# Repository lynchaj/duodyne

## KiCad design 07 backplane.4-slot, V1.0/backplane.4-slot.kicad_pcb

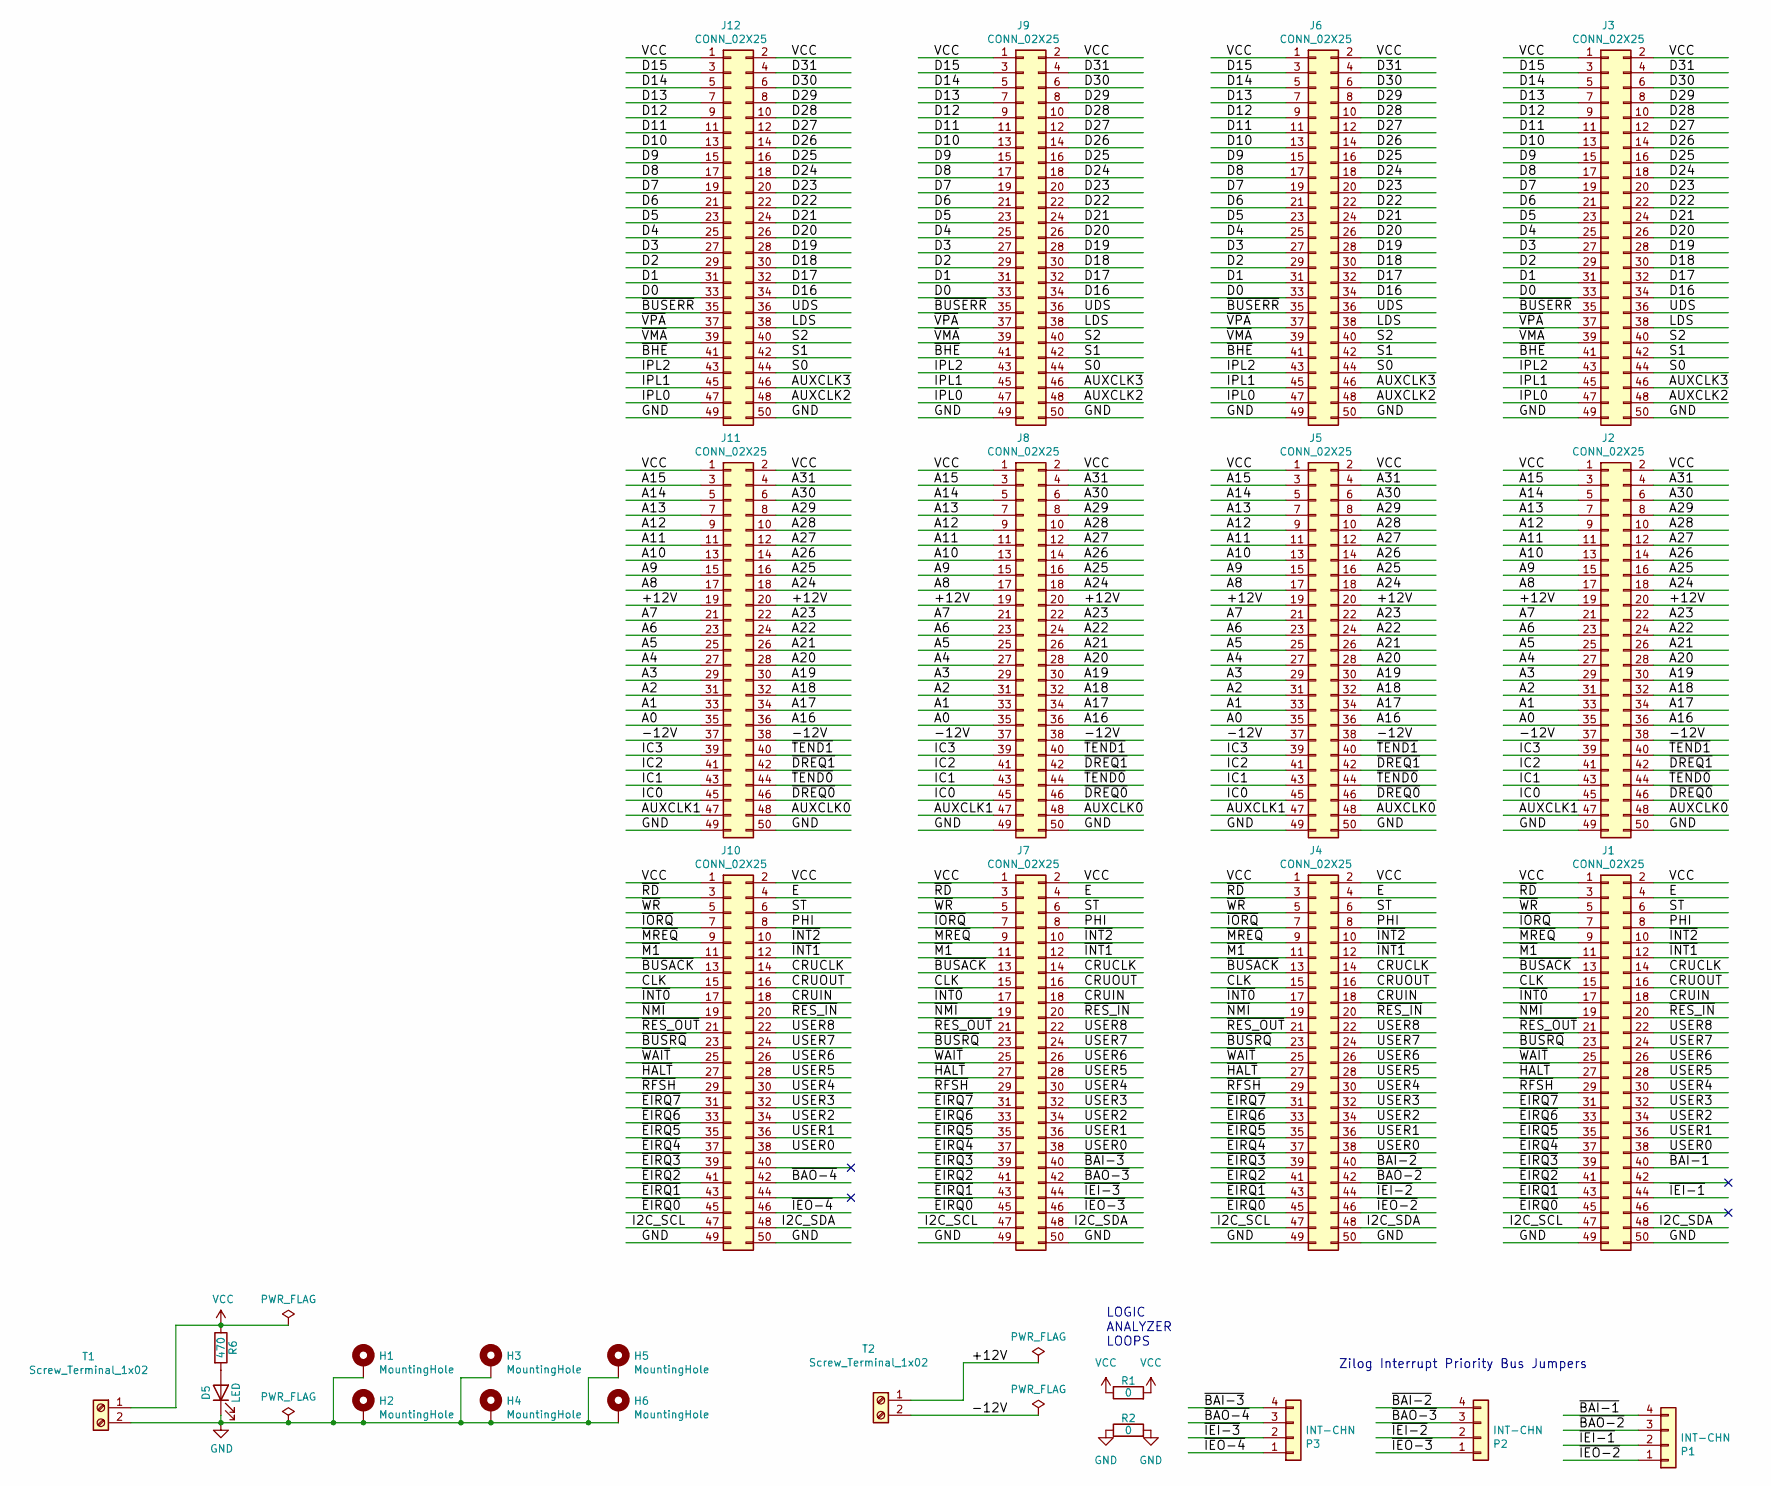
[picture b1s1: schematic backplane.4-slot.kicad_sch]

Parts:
D5: LED; LED_D3.0mm
H1, H2, H3, H4, H5, H6: MountingHole; MountingHole_3.2mm_M3_Pad
J1, J2, J3, J4, J5, J6, J7, J8, J9, J10, J11, J12: CONN_02X25; PinSocket_2x25_P2.54mm_Vertical
P1, P2, P3: INT-CHN; PinHeader_1x04_P2.54mm_Vertical
R1, R2: 0; R_Axial_DIN0207_L6.3mm_D2.5mm_P7.62mm_Horizontal
R6: 470; R_Axial_DIN0207_L6.3mm_D2.5mm_P7.62mm_Horizontal
T1, T2: Screw_Terminal_1x02; TerminalBlock_Phoenix_MKDS-1,5-2-5.08_1x02_P5.08mm_Horizont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

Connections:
/+12V: J2.19, J2.20, J5.19, J5.20, J8.19, J8.20, J11.19, J11.20, T2.1
/-12V: J2.37, J2.38, J5.37, J5.38, J8.37, J8.38, J11.37, J11.38, T2.2
/A0: J2.35, J5.35, J8.35, J11.35
/A1: J2.33, J5.33, J8.33, J11.33
/A2: J2.31, J5.31, J8.31, J11.31
/A3: J2.29, J5.29, J8.29, J11.29
/A4: J2.27, J5.27, J8.27, J11.27
/A5: J2.25, J5.25, J8.25, J11.25
/A6: J2.23, J5.23, J8.23, J11.23
/A7: J2.21, J5.21, J8.21, J11.21
/A8: J2.17, J5.17, J8.17, J11.17
/A9: J2.15, J5.15, J8.15, J11.15
/A10: J2.13, J5.13, J8.13, J11.13
/A11: J2.11, J5.11, J8.11, J11.11
/A12: J2.9, J5.9, J8.9, J11.9
/A13: J2.7, J5.7, J8.7, J11.7
/A14: J2.5, J5.5, J8.5, J11.5
/A15: J2.3, J5.3, J8.3, J11.3
/A16: J2.36, J5.36, J8.36, J11.36
/A17: J2.34, J5.34, J8.34, J11.34
/A18: J2.32, J5.32, J8.32, J11.32
/A19: J2.30, J5.30, J8.30, J11.30
/A20: J2.28, J5.28, J8.28, J11.28
/A21: J2.26, J5.26, J8.26, J11.26
/A22: J2.24, J5.24, J8.24, J11.24
/A23: J2.22, J5.22, J8.22, J11.22
/A24: J2.18, J5.18, J8.18, J11.18
/A25: J2.16, J5.16, J8.16, J11.16
/A26: J2.14, J5.14, J8.14, J11.14
/A27: J2.12, J5.12, J8.12, J11.12
/A28: J2.10, J5.10, J8.10, J11.10
/A29: J2.8, J5.8, J8.8, J11.8
/A30: J2.6, J5.6, J8.6, J11.6
/A31: J2.4, J5.4, J8.4, J11.4
/AUXCLK0: J2.48, J5.48, J8.48, J11.48
/AUXCLK1: J2.47, J5.47, J8.47, J11.47
/AUXCLK2: J3.48, J6.48, J9.48, J12.48
/AUXCLK3: J3.46, J6.46, J9.46, J12.46
/CLK: J1.15, J4.15, J7.15, J10.15
/CRUCLK: J1.14, J4.14, J7.14, J10.14
/CRUIN: J1.18, J4.18, J7.18, J10.18
/CRUOUT: J1.16, J4.16, J7.16, J10.16
/D0: J3.33, J6.33, J9.33, J12.33
/D1: J3.31, J6.31, J9.31, J12.31
/D2: J3.29, J6.29, J9.29, J12.29
/D3: J3.27, J6.27, J9.27, J12.27
/D4: J3.25, J6.25, J9.25, J12.25
/D5: J3.23, J6.23, J9.23, J12.23
/D6: J3.21, J6.21, J9.21, J12.21
/D7: J3.19, J6.19, J9.19, J12.19
/D8: J3.17, J6.17, J9.17, J12.17
/D9: J3.15, J6.15, J9.15, J12.15
/D10: J3.13, J6.13, J9.13, J12.13
/D11: J3.11, J6.11, J9.11, J12.11
/D12: J3.9, J6.9, J9.9, J12.9
/D13: J3.7, J6.7, J9.7, J12.7
/D14: J3.5, J6.5, J9.5, J12.5
/D15: J3.3, J6.3, J9.3, J12.3
/D16: J3.34, J6.34, J9.34, J12.34
/D17: J3.32, J6.32, J9.32, J12.32
/D18: J3.30, J6.30, J9.30, J12.30
/D19: J3.28, J6.28, J9.28, J12.28
/D20: J3.26, J6.26, J9.26, J12.26
/D21: J3.24, J6.24, J9.24, J12.24
/D22: J3.22, J6.22, J9.22, J12.22
/D23: J3.20, J6.20, J9.20, J12.20
/D24: J3.18, J6.18, J9.18, J12.18
/D25: J3.16, J6.16, J9.16, J12.16
/D26: J3.14, J6.14, J9.14, J12.14
/D27: J3.12, J6.12, J9.12, J12.12
/D28: J3.10, J6.10, J9.10, J12.10
/D29: J3.8, J6.8, J9.8, J12.8
/D30: J3.6, J6.6, J9.6, J12.6
/D31: J3.4, J6.4, J9.4, J12.4
/E: J1.4, J4.4, J7.4, J10.4
/I2C_SCL: J1.47, J4.47, J7.47, J10.47
/I2C_SDA: J1.48, J4.48, J7.48, J10.48
/IC0: J2.45, J5.45, J8.45, J11.45
/IC1: J2.43, J5.43, J8.43, J11.43
/IC2: J2.41, J5.41, J8.41, J11.41
/IC3: J2.39, J5.39, J8.39, J11.39
/IPL0: J3.47, J6.47, J9.47, J12.47
/IPL1: J3.45, J6.45, J9.45, J12.45
/IPL2: J3.43, J6.43, J9.43, J12.43
/LDS: J3.38, J6.38, J9.38, J12.38
/PHI: J1.8, J4.8, J7.8, J10.8
/S0: J3.44, J6.44, J9.44, J12.44
/S1: J3.42, J6.42, J9.42, J12.42
/S2: J3.40, J6.40, J9.40, J12.40
/ST: J1.6, J4.6, J7.6, J10.6
/UDS: J3.36, J6.36, J9.36, J12.36
/USER0: J1.38, J4.38, J7.38, J10.38
/USER1: J1.36, J4.36, J7.36, J10.36
/USER2: J1.34, J4.34, J7.34, J10.34
/USER3: J1.32, J4.32, J7.32, J10.32
/USER4: J1.30, J4.30, J7.30, J10.30
/USER5: J1.28, J4.28, J7.28, J10.28
/USER6: J1.26, J4.26, J7.26, J10.26
/USER7: J1.24, J4.24, J7.24, J10.24
/USER8: J1.22, J4.22, J7.22, J10.22
/~BAI-1: J1.40, P1.4
/~BAI-2: J4.40, P2.4
/~BAI-3: J7.40, P3.4
/~BAO-2: J4.42, P1.3
/~BAO-3: J7.42, P2.3
/~BAO-4: J10.42, P3.3
/~BHE: J3.41, J6.41, J9.41, J12.41
/~BUSACK: J1.13, J4.13, J7.13, J10.13
/~BUSERR: J3.35, J6.35, J9.35, J12.35
/~BUSRQ: J1.23, J4.23, J7.23, J10.23
/~DREQ0: J2.46, J5.46, J8.46, J11.46
/~DREQ1: J2.42, J5.42, J8.42, J11.42
/~EIRQ0: J1.45, J4.45, J7.45, J10.45
/~EIRQ1: J1.43, J4.43, J7.43, J10.43
/~EIRQ2: J1.41, J4.41, J7.41, J10.41
/~EIRQ3: J1.39, J4.39, J7.39, J10.39
/~EIRQ4: J1.37, J4.37, J7.37, J10.37
/~EIRQ5: J1.35, J4.35, J7.35, J10.35
/~EIRQ6: J1.33, J4.33, J7.33, J10.33
/~EIRQ7: J1.31, J4.31, J7.31, J10.31
/~HALT: J1.27, J4.27, J7.27, J10.27
/~IEI-1: J1.44, P1.2
/~IEI-2: J4.44, P2.2
/~IEI-3: J7.44, P3.2
/~IEO-2: J4.46, P1.1
/~IEO-3: J7.46, P2.1
/~IEO-4: J10.46, P3.1
/~INT0: J1.17, J4.17, J7.17, J10.17
/~INT1: J1.12, J4.12, J7.12, J10.12
/~INT2: J1.10, J4.10, J7.10, J10.10
/~IORQ: J1.7, J4.7, J7.7, J10.7
/~M1: J1.11, J4.11, J7.11, J10.11
/~MREQ: J1.9, J4.9, J7.9, J10.9
/~NMI: J1.19, J4.19, J7.19, J10.19
/~RD: J1.3, J4.3, J7.3, J10.3
/~RES_IN: J1.20, J4.20, J7.20, J10.20
/~RES_OUT: J1.21, J4.21, J7.21, J10.21
/~RFSH: J1.29, J4.29, J7.29, J10.29
/~TEND0: J2.44, J5.44, J8.44, J11.44
/~TEND1: J2.40, J5.40, J8.40, J11.40
/~VMA: J3.39, J6.39, J9.39, J12.39
/~VPA: J3.37, J6.37, J9.37, J12.37
/~WAIT: J1.25, J4.25, J7.25, J10.25
/~WR: J1.5, J4.5, J7.5, J10.5
GND: D5.1 (K), H1.1, H2.1, H3.1, H4.1, H5.1, H6.1, J1.49, J1.50, J2.49, J2.50, J3.49, J3.50, J4.49, J4.50, J5.49, J5.50, J6.49, J6.50, J7.49, J7.50, J8.49, J8.50, J9.49, J9.50, J10.49, J10.50, J11.49, J11.50, J12.49, J12.50, R2.1, R2.2, T1.2
unnamed: D5.2 (A), R6.2
VCC: J1.1, J1.2, J2.1, J2.2, J3.1, J3.2, J4.1, J4.2, J5.1, J5.2, J6.1, J6.2, J7.1, J7.2, J8.1, J8.2, J9.1, J9.2, J10.1, J10.2, J11.1, J11.2, J12.1, J12.2, R1.1, R1.2, R6.1, T1.1

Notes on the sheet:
LOGIC ANALYZER LOOPS
Zilog Interrupt Priority Bus Jumpers

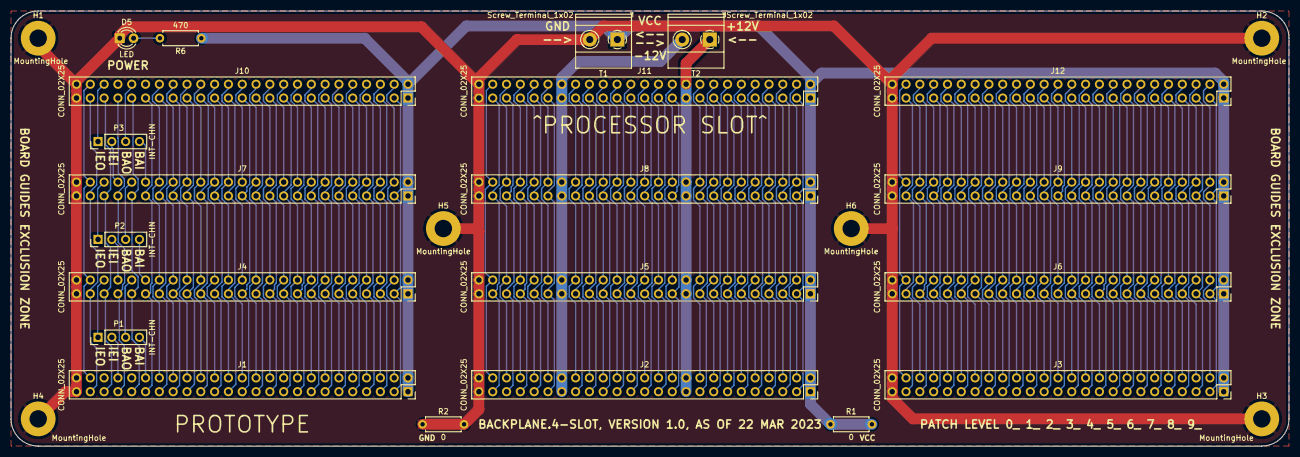
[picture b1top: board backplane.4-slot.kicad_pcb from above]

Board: 2 copper layers, 235.0 x 80.0 mm, 27 parts (0 on the bottom side), 147 nets.

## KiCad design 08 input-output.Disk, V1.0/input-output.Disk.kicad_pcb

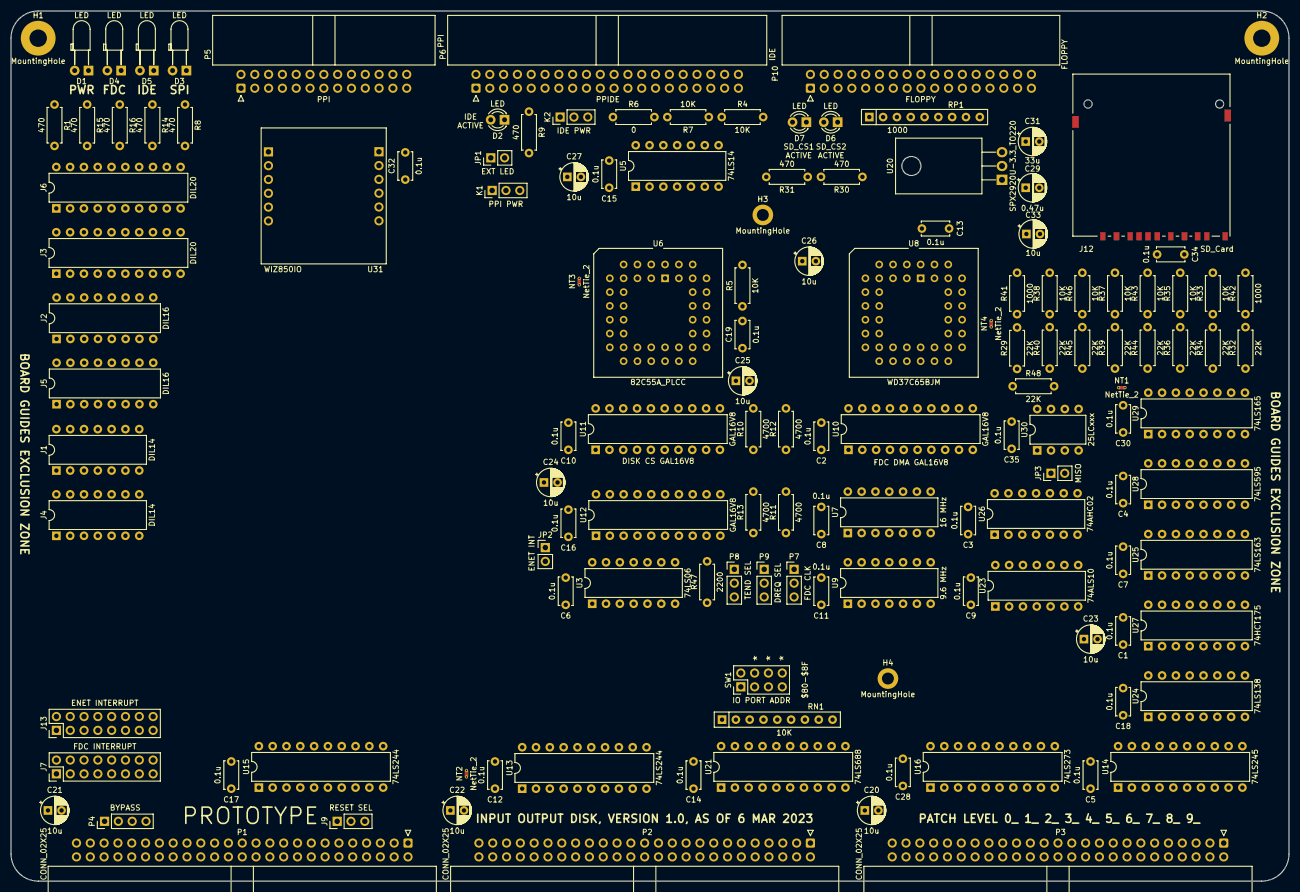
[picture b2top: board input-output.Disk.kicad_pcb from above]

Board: 2 copper layers, 235.0 x 160.0 mm, 136 parts (0 on the bottom side), 202 nets, no tracks yet.

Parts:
C1, C2, C3, C4, C5, C6, C7, C8, C9, C10, C11, C12, C13, C14, C15, C16, C17, C18, C19, C28, C30, C32, C34, C35: 0.1u; C_Disc_D5.0mm_W2.5mm_P5.00mm
C20, C21, C22, C23, C24, C25, C26, C27, C33: 10u; CP_Radial_D5.0mm_P2.50mm
C29: 0.47u; CP_Radial_D5.0mm_P2.50mm
C31: 33u; CP_Radial_D5.0mm_P2.50mm
D1, D3, D4, D5: LED; LED_D3.0mm_Horizontal_O3.81mm_Z2.0mm
D2, D6, D7: LED; LED_D3.0mm
H1, H2: MountingHole; MountingHole_3.2mm_M3_Pad
H3, H4: MountingHole; MountingHole_2.2mm_M2_DIN965_Pad
J1, J4: DIL14; DIP-14_W7.62mm
J2, J5: DIL16; DIP-16_W7.62mm
J3, J6: DIL20; DIP-20_W7.62mm
J7: FDC INTERRUPT; PinHeader_2x08_P2.54mm_Vertical
J9: RESET SEL; PinHeader_1x03_P2.54mm_Vertical
J12: SD_Card; SD_Card_Receptacle
J13: ENET INTERRUPT; PinHeader_2x08_P2.54mm_Vertical
JP1: EXT LED; PinHeader_1x02_P2.54mm_Vertical
JP2: ENET INT; PinHeader_1x02_P2.54mm_Vertical
JP3: MISO; PinHeader_1x02_P2.54mm_Vertical
K1: PPI PWR; PinHeader_1x03_P2.54mm_Vertical
K2: IDE PWR; PinHeader_1x03_P2.54mm_Vertical
NT1, NT2, NT3, NT4: NetTie_2; NetTie-2_THT_Pad0.3mm
P1, P2, P3: CONN_02X25; IDC-Header_2x25_P2.54mm_Horizontal
P4: BYPASS; PinHeader_1x04_P2.54mm_Vertical
P5: PPI; IDC-Header_2x13_P2.54mm_Horizontal
P6: IDE; IDC-Header_2x20_P2.54mm_Horizontal
P7: FDC CLK; PinHeader_1x03_P2.54mm_Vertical
P8: TEND SEL; PinHeader_1x03_P2.54mm_Vertical
P9: DREQ SEL; PinHeader_1x03_P2.54mm_Vertical
P10: FLOPPY; IDC-Header_2x17_P2.54mm_Horizontal
R1, R8, R9, R14, R15, R16, R30, R31: 470; R_Axial_DIN0207_L6.3mm_D2.5mm_P7.62mm_Horizontal
R4, R5, R7, R33, R35, R37, R38, R43, R46: 10K; R_Axial_DIN0207_L6.3mm_D2.5mm_P7.62mm_Horizontal
R6: 0; R_Axial_DIN0207_L6.3mm_D2.5mm_P7.62mm_Horizontal
R10, R11, R12, R13: 4700; R_Axial_DIN0207_L6.3mm_D2.5mm_P7.62mm_Horizontal
R29, R32, R34, R36, R39, R40, R44, R45, R48: 22K; R_Axial_DIN0207_L6.3mm_D2.5mm_P7.62mm_Horizontal
R41, R42: 1000; R_Axial_DIN0207_L6.3mm_D2.5mm_P7.62mm_Horizontal
R47: 2200; R_Axial_DIN0207_L6.3mm_D2.5mm_P7.62mm_Horizontal
RN1: 10K; R_Array_SIP9
RP1: 1000; R_Array_SIP9
SW1: IO PORT ADDR; PinHeader_2x04_P2.54mm_Vertical
U3: 74LS06; DIP-14_W7.62mm
U5: 74LS14; DIP-14_W7.62mm
U6: 82C55A_PLCC; PLCC-44_THT-Socket
U7: 16 MHz; DIP-14_W7.62mm
U8: WD37C65BJM; PLCC-44_THT-Socket
U9: 9.6 MHz; DIP-14_W7.62mm
U10, U11, U12: GAL16V8; DIP-20_W7.62mm
U13, U15: 74LS244; DIP-20_W7.62mm
U14: 74LS245; DIP-20_W7.62mm
U16: 74LS273; DIP-20_W7.62mm
U20: SPX2920U-3.3_TO220; TO-220-3_Horizontal_TabDown
U21: 74LS688; DIP-20_W7.62mm
U23: 74ALS10; DIP-14_W7.62mm
U24: 74LS138; DIP-16_W7.62mm
U25: 74LS163; DIP-16_W7.62mm
U26: 74AHC02; DIP-14_W7.62mm
U27: 74HCT175; DIP-16_W7.62mm
U28: 74LS595; DIP-16_W7.62mm
U29: 74LS165; DIP-16_W7.62mm
U30: 25LCxxx; DIP-8_W7.62mm
U31: WIZ850IO

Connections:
16MHZ-CLK: U7.8, U7.11, U8.26 (XT1)
+12V: P2.19, P2.20
-12V: P2.37, P2.38
/FDC/FDC_DMA: R12.2, U3.1, U8.15 (DMA)
/FDC/GND_PLCC: NT4.2, U8.34 (GND)
/FDC/PCVAL: RP1.8 (R7), U8.27 (PCVAL)
/FDC/RDY: P9.2, R11.1, U3.2
/FDC/~DCHG: P10.34, RP1.4 (R3), U8.40 (/DCHG)
/FDC/~DIRC: P10.18, U8.31 (/DIRC)
/FDC/~DS1: P10.14, U8.33 (/DS1)
/FDC/~DS2: P10.12, U8.35 (/DS2)
/FDC/~HS: P10.32, U8.28 (/HS)
/FDC/~IDX: P10.8, RP1.7 (R6), U8.43 (/IDX)
/FDC/~INT_FDC: J7.1, J7.3, J7.5, J7.7, J7.9, J7.11, J7.13, J7.15, U3.12
/FDC/~MO1: P10.10, U8.36 (/MO1/DS3)
/FDC/~MO2: P10.16, U8.37 (/MO2/DS4)
/FDC/~RDD: P10.30, RP1.3 (R2), U8.21 (/RDD)
/FDC/~RWC: P10.2, U8.39 (/RWC/RPM)
/FDC/~STEP: P10.20, U8.32 (/STEP)
/FDC/~TR00: P10.26, RP1.6 (R5), U8.42 (/TR00)
/FDC/~WD: P10.22, U8.30 (/WD)
/FDC/~WE: P10.24, U8.29 (/WE)
/FDC/~WP: P10.28, RP1.5 (R4), U8.41 (/WP)
/GAL/~CS_FDC_LED: D4.1 (K), U10.12 (IO8)
/PPIDE/CSEL: P6.28, R6.2
/PPIDE/DMARQ: P6.21, R7.2
/PPIDE/GND_PLCC: NT3.2, U6.8 (GND)
/PPIDE/PA0: P5.2, P6.17, U6.5 (PA0)
/PPIDE/PA1: P5.4, P6.15, U6.4 (PA1)
/PPIDE/PA2: P5.6, P6.13, U6.3 (PA2)
/PPIDE/PA3: P5.8, P6.11, U6.2 (PA3)
/PPIDE/PA4: P5.10, P6.9, U6.44 (PA4)
/PPIDE/PA5: P5.12, P6.7, U6.43 (PA5)
/PPIDE/PA6: P5.14, P6.5, U6.42 (PA6)
/PPIDE/PA7: P5.16, P6.3, R5.2, U6.41 (PA7)
/PPIDE/PB0: P5.18, P6.4, U6.20 (PB0)
/PPIDE/PB1: P5.20, P6.6, U6.21 (PB1)
/PPIDE/PB2: P5.22, P6.8, U6.22 (PB2)
/PPIDE/PB3: P5.24, P6.10, U6.24 (PB3)
/PPIDE/PB4: P5.23, P6.12, U6.25 (PB4)
/PPIDE/PB5: P5.21, P6.14, U6.26 (PB5)
/PPIDE/PB6: P5.19, P6.16, U6.27 (PB6)
/PPIDE/PB7: P5.17, P6.18, U6.28 (PB7)
/PPIDE/PC0: P5.1, P6.35, U6.16 (PC0)
/PPIDE/PC1: P5.3, P6.33, U6.17 (PC1)
/PPIDE/PC2: P5.5, P6.36, U6.18 (PC2)
/PPIDE/PC3: P5.7, U5.1, U6.19 (PC3)
/PPIDE/PC4: P5.9, U5.5, U6.15 (PC4)
/PPIDE/PC5: P5.11, U5.3, U6.14 (PC5)
/PPIDE/PC6: P5.13, U5.13, U6.13 (PC6)
/PPIDE/PC7: P5.15, U5.9, U6.11 (PC7)
/PPIDE/VCC_IDE: K2.2, P6.20
/PPIDE/VCC_PP: K1.2, P5.25
/PPIDE/~ACTIVE: D2.1 (K), JP1.2 (B), P6.39
/PPIDE/~DMACK: P6.29, R4.2
/PPIDE/~PC3: P6.37, U5.2
/PPIDE/~PC4: P6.38, U5.6
/PPIDE/~PC5: P6.23, U5.4
/PPIDE/~PC6: P6.25, U5.12
/PPIDE/~PC7: P6.1, U5.8
/WIZNET/D0: U28.15 (QA), U29.11 (D0)
/WIZNET/D1: U28.1 (QB), U29.12 (D1)
/WIZNET/D2: U28.2 (QC), U29.13 (D2)
/WIZNET/D3: U28.3 (QD), U29.14 (D3)
/WIZNET/D4: U28.4 (QE), U29.3 (D4)
/WIZNET/D5: U28.5 (QF), U29.4 (D5)
/WIZNET/D6: U28.6 (QG), U29.5 (D6)
/WIZNET/D7: U28.7 (QH), U29.6 (D7)
/WIZNET/MISO: J12.7 (DAT0), JP3.2 (B), R32.2, U28.14 (SER), U31.J2-6 (MISO)
/WIZNET/MOSI: J12.2 (CMD), R43.2, R44.2, U30.5 (MOSI), U31.J1-3 (MOSI)
/WIZNET/QD: U25.5 (D2), U25.6 (D3), U25.11 (Q3), U26.3, U26.6, U29.15 (~CE)
/WIZNET/RCO: U23.4, U25.15 (TC)
/WIZNET/SCK: J12.5 (CLK), R35.2, R36.2, U28.11 (SRCLK), U30.6 (SCK), U31.J1-4 (SCLK)
/WIZNET/~CLR: U23.6, U23.9, U25.1 (~MR)
/WIZNET/~CS0: R38.2, R40.2, U31.J1-5 (~SCN)
/WIZNET/~CS1: R33.2, R34.1, U30.1 (~CS)
/WIZNET/~CS2: J12.1 (CD/DAT3), R37.2, R39.2
/WIZNET/~CTRL_WR: U24.11 (O4), U27.9 (Cp)
/WIZNET/~ENET_INT: JP2.1 (A), U3.9
/WIZNET/~LATCH_WR: U16.11 (Cp), U24.10 (O5)
/WIZNET/~MOSI: U26.11, U29.7 (~Q7)
/WIZNET/~QD: U25.7 (CEP), U25.9 (~PE), U26.4
/WIZNET/~RST: R45.2, R46.2, U31.J2-5 (~RST)
/WIZNET/~SD_RDNTR: U23.1, U24.13 (O2)
/WIZNET/~SD_RDTR: U23.2, U23.3, U23.11, U23.13, U24.12 (O3)
/WIZNET/~SD_WRTR: U23.5, U23.10, U24.15 (O0), U29.1 (~PL)
/WIZNET/~SER_RD: U26.10, U28.13 (~OE)
/WIZNET/~TR: U23.8, U25.3 (D0), U25.4 (D1)
A0: P2.35, U13.2 (I0a)
A1: P2.33, U13.4 (I1a)
A2: P2.31, U13.6 (I2a)
A3: P2.29, U13.8 (I3a)
A4: P2.27, U13.11 (I0b)
A5: P2.25, U13.13 (I1b)
A6: P2.23, U13.15 (I2b)
A7: P2.21, U13.17 (I3b)
CLK: P1.15, U15.8 (I3a)
D0: P3.33, U14.2 (A0)
D1: P3.31, U14.3 (A1)
D2: P3.29, U14.4 (A2)
D3: P3.27, U14.5 (A3)
D4: P3.25, U14.6 (A4)
D5: P3.23, U14.7 (A5)
D6: P3.21, U14.8 (A6)
D7: P3.19, U14.9 (A7)
FDC-RESET: U8.20 (RST), U10.19 (IO1)
FDC-TC: U8.6 (TC), U10.18 (IO2)
GND: C1.2, C2.2, C3.2, C4.2, C5.2, C6.2, C7.2, C8.2, C9.2, C10.2, C11.2, C12.2, C13.2, C14.2, C15.2, C16.2, C17.2, C18.2, C19.2, C20.2, C21.2, C22.2, C23.2, C24.2, C25.2, C26.2, C27.2, C28.2, C29.2, C30.2, C31.2, C32.2, C33.2, C34.2, C35.2, D1.1 (K), D6.1 (K), D7.1 (K), H1.1, H2.1, J12.3 (VSS), J12.6 (VSS), J12.12 (SHELL1), J12.13 (SHELL2), K1.1, K2.1, NT2.1, NT3.1, NT4.1, P1.49, P1.50, P2.49, P2.50, P3.49, P3.50, P5.26, P6.2, P6.19, P6.22, P6.24, P6.26, P6.30, P6.40, P7.3, P10.1, P10.3, P10.5, P10.7, P10.9, P10.11, P10.13, P10.15, P10.17, P10.19, P10.21, P10.23, P10.25, P10.27, P10.29, P10.31, P10.33, R5.1, R6.1, R7.1, R10.1, R12.1, R34.2, R36.1, R39.1, R40.1, R44.1, R45.1, U3.7 (GND), U5.7 (GND), U7.4, U7.7, U9.4, U9.7, U10.10 (GND), U11.10 (GND), U12.10 (GND), U13.10 (GND), U14.10 (GND), U15.10 (GND), U16.10 (GND), U20.2 (GND), U21.10 (GND), U23.7 (GND), U24.8 (GND), U25.8 (GND), U26.7 (GND), U27.8 (GND), U28.8 (GND), U29.8 (GND), U30.4 (GND), U31.J1-1 (GND), U31.J1-2 (GND), U31.J2-1 (GND)
INT_FDC: R10.2, U3.13, U8.16 (IRQ)
unnamed: D1.2 (A), R1.1
unnamed: D2.2 (A), R8.1
unnamed: D3.1 (K), U11.16 (IO4)
unnamed: D3.2 (A), R14.1
unnamed: D4.2 (A), R15.1
unnamed: D5.1 (K), U11.15 (IO5)
unnamed: D5.2 (A), R16.1
unnamed: D6.2 (A), R30.2
unnamed: D7.2 (A), R31.2
unnamed: J9.2, U15.2 (I0a)
unnamed: J12.8 (DAT1), R42.2
unnamed: J12.9 (DAT2), R41.1
unnamed: J13.1, J13.3, J13.5, J13.7, J13.9, J13.11, J13.13, J13.15, U3.10
unnamed: JP1.1 (A), R9.1
unnamed: JP2.2 (B), U31.J1-6 (~INT)
unnamed: JP3.1 (A), U30.2 (MISO)
unnamed: P7.1, U9.8, U9.11
unnamed: P7.2, U8.23 (XT2)
unnamed: R29.2, U30.7 (~HOLD)
unnamed: R30.1, U27.7 (Q1)
unnamed: R31.1, U27.2 (Q0)
unnamed: R33.1, U27.3 (~Q0)
unnamed: R35.1, U26.1
unnamed: R37.1, U27.6 (~Q1)
unnamed: R38.1, U27.11 (~Q2)
unnamed: R43.1, U26.13
unnamed: R46.1, U27.14 (~Q3)
unnamed: R47.2, U3.8, U3.11
unnamed: R48.2, U30.3 (~WP)
unnamed: RN1.2 (R1), SW1.1, U21.18 (R7)
unnamed: RN1.3 (R2), SW1.3, U21.16 (R6)
unnamed: RN1.4 (R3), SW1.5, U21.14 (R5)
unnamed: RN1.5 (R4), SW1.7, U21.12 (R4)
unnamed: RN1.9 (R8), U21.3 (R0), U21.4 (P1), U21.5 (R1), U21.6 (P2), U21.7 (R2), U21.8 (P3), U21.9 (R3)
unnamed: U5.10, U6.39 (RESET)
unnamed: U23.12, U26.9
ONE: NT1.2, U25.10 (CET), U28.10 (~SRCLR), U29.10 (DS)
VCC: C1.1, C2.1, C3.1, C4.1, C5.1, C6.1, C7.1, C8.1, C9.1, C10.1, C11.1, C12.1, C13.1, C14.1, C15.1, C16.1, C17.1, C18.1, C19.1, C20.1, C21.1, C22.1, C23.1, C24.1, C25.1, C26.1, C27.1, C28.1, C29.1, C30.1, K1.3, K2.3, NT1.1, P1.1, P1.2, P2.1, P2.2, P3.1, P3.2, R1.2, R4.1, R8.2, R9.2, R11.2, R13.2, R14.2, R15.2, R16.2, R47.1, RN1.1 (common), RP1.1 (common), U3.14 (VCC), U5.14 (VCC), U6.29 (VCC), U7.1, U7.14, U8.44 (VCC), U9.1, U9.14, U10.20 (VCC), U11.20 (VCC), U12.20 (VCC), U13.20 (VCC), U14.20 (VCC), U15.20 (VCC), U16.20 (VCC), U20.1 (VI), U21.20 (VCC), U23.14 (VCC), U24.16 (VCC), U25.16 (VCC), U26.14 (VCC), U27.16 (VCC), U28.16 (VCC), U29.16 (VCC)
VDD: C31.1, C32.1, C33.1, C34.1, C35.1, J12.4 (VDD), R29.1, R32.1, R41.2, R42.1, R48.1, U20.3 (VO), U30.8 (VCC), U31.J2-2 (VDD), U31.J2-3 (VDD)
ZERO: NT2.2, SW1.2, SW1.4, SW1.6, SW1.8, U8.17 (/DCHGEN), U8.24 (DRV), U13.1 (OEa), U13.19 (OEb), U15.1 (OEa), U15.19 (OEb), U26.5, U26.8, U26.12
bA0: U6.10 (A0), U8.4 (A0), U10.5 (I5), U13.18 (O0a), U24.1 (A0)
bA1: U6.9 (A1), U10.6 (I6), U13.16 (O1a), U24.3 (A2)
bA2: U10.7 (I7), U11.4 (I4), U13.14 (O2a)
bA3: U11.3 (I3), U13.12 (O3a)
bA4: U13.9 (O0b), U21.11 (P4)
bA5: U13.7 (O1b), U21.13 (P5)
bA6: U13.5 (O2b), U21.15 (P6)
bA7: U13.3 (O3b), U21.17 (P7)
bCLK: U15.12 (O3a), U25.2 (CP), U26.2, U28.12 (RCLK), U29.2 (CP)
bD0: U6.38 (D0), U8.7 (DB0), U14.18 (B0), U16.3 (D0), U27.13 (D3)
bD1: U6.37 (D1), U8.8 (DB1), U14.17 (B1), U16.4 (D1)
bD2: U6.36 (D2), U8.9 (DB2), U14.16 (B2), U16.7 (D2)
bD3: U6.35 (D3), U8.10 (DB3), U14.15 (B3), U16.8 (D3), U27.12 (D2)
bD4: U6.33 (D4), U8.11 (DB4), U14.14 (B4), U16.13 (D4), U27.4 (D0)
bD5: U6.32 (D5), U8.12 (DB5), U14.13 (B5), U16.14 (D5), U27.5 (D1)
bD6: U6.31 (D6), U8.13 (DB6), U14.12 (B6), U16.17 (D6)
bD7: U6.30 (D7), U8.14 (DB7), U14.11 (B7), U16.18 (D7)
~BAI: P1.40, P4.4
~BAO: P1.42, P4.3
~CS_DISK: U11.2 (I2), U14.19 (CE), U21.19 (P=R)
~CS_FDC: U10.4 (I4), U11.19 (IO1)
~CS_PPIDE: U6.7 (~CS), U11.18 (IO2)
~CS_SPI: U11.17 (I03), U24.5 (E2)
~DREQ0: P2.46, P9.1
~DREQ1: P2.42, P9.3
~EIRQ0: J7.2, J13.2, P1.45
~EIRQ1: J7.4, J13.4, P1.43
~EIRQ2: J7.6, J13.6, P1.41
~EIRQ3: J7.8, J13.8, P1.39
~EIRQ4: J7.10, J13.10, P1.37
~EIRQ5: J7.12, J13.12, P1.35
~EIRQ6: J7.14, J13.14, P1.33
~EIRQ7: J7.16, J13.16, P1.31
~FDC-DACK: U8.5 (/DACK), U10.14 (IO6)
~IEI: P1.44, P4.2
~IEO: P1.46, P4.1
~IORQ: P1.7, U15.11 (I0b)
~LDCR: U8.19 (/LDCR), U10.15 (IO5)
~LDOR: U8.18 (/LDOR), U10.13 (IO7)
~M1: P1.11, U15.13 (I1b)
~MSR-DATA: U8.3 (/CS), U10.17 (I03)
~PULSE: P8.2, R13.1, U10.3 (I3)
~RD: P1.3, U14.1 (A->B), U15.17 (I3b)
~RES_IN: J9.1, P1.20
~RES_OUT: J9.3, P1.21
~TEND0: P2.44, P8.1
~TEND1: P2.40, P8.3
~WR: P1.5, U15.15 (I2b)
~bIORQ: U15.9 (O0b), U21.1 (G), U24.4 (E1)
~bM1: U15.7 (O1b), U21.2 (P0), U24.6 (E3)
~bRD: U6.6 (~RD), U8.1 (/RD), U10.8 (I8), U15.3 (O3b)
~bRESET: U5.11, U10.2 (I2), U15.18 (O0a), U16.1 (~Mr), U27.1 (~Mr)
~bWR: U6.40 (~WR), U8.2 (/WR), U10.9 (I9), U15.5 (O2b), U24.2 (A1)

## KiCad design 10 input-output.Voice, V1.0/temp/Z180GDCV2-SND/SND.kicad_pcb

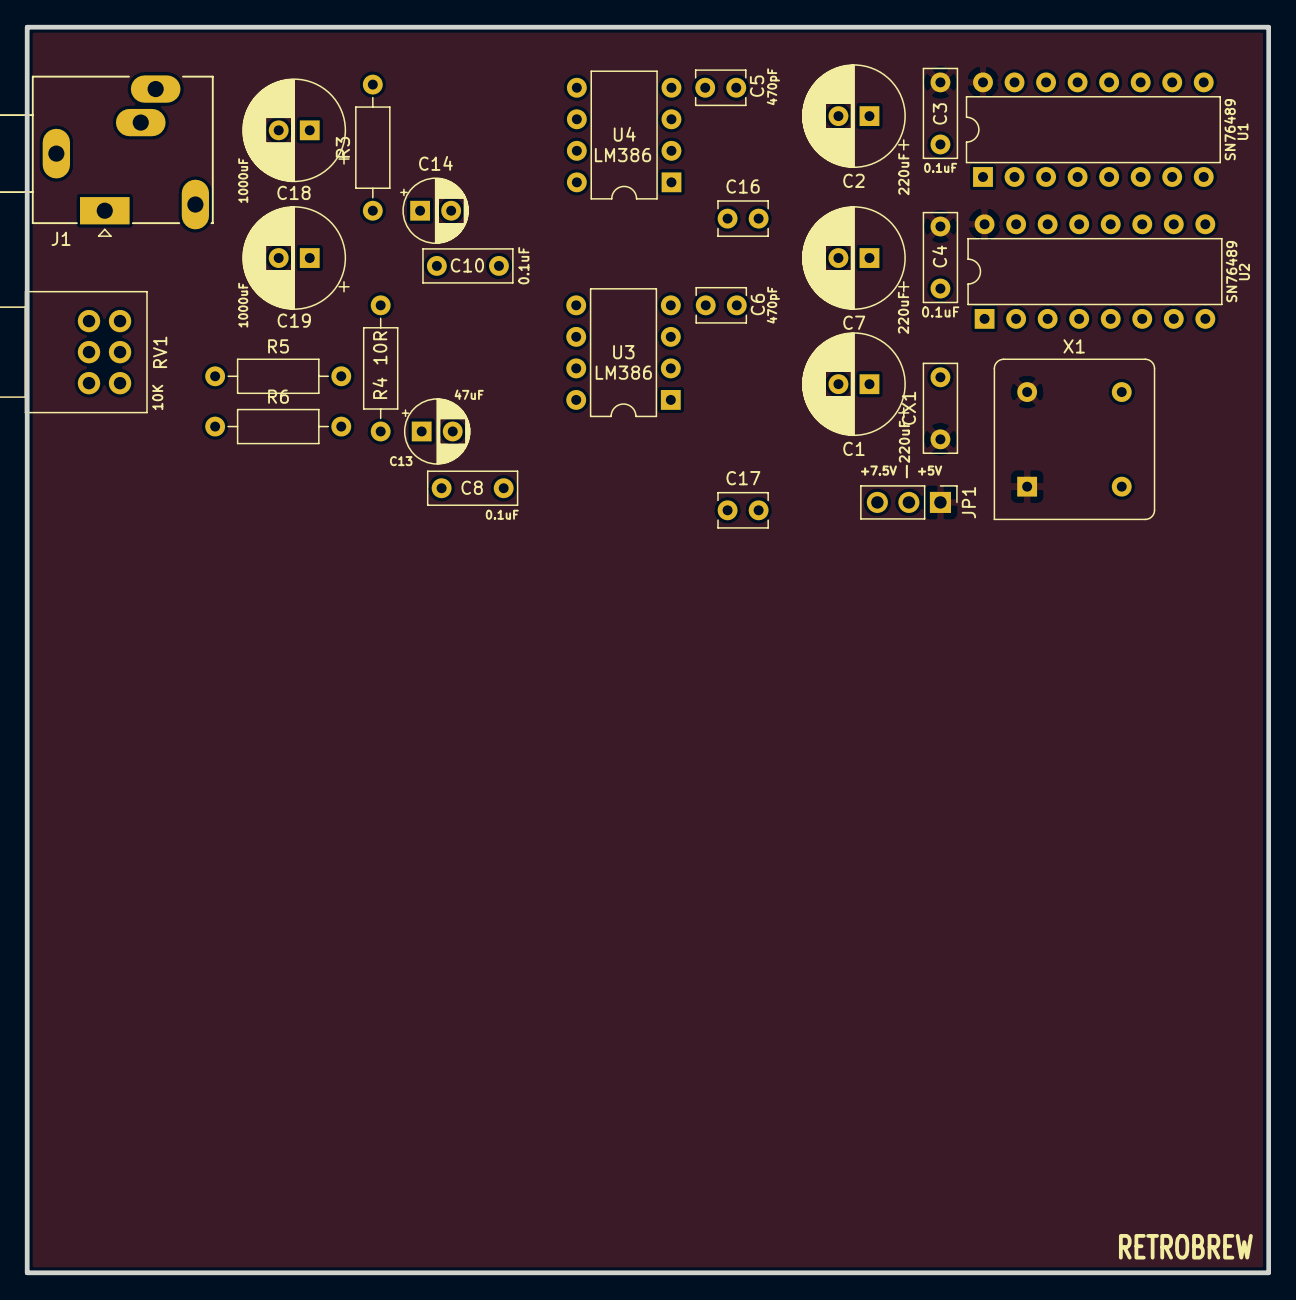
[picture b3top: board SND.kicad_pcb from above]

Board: 2 copper layers, 100.0 x 100.3 mm, 28 parts (0 on the bottom side), 28 nets, no tracks yet.

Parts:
C1, C2, C7: 220uF; CP_Radial_D8.0mm_P2.50mm
C3, C4, C8, C10: 0.1uF; C_Disc_D7.0mm_W2.5mm_P5.00mm
C5, C6: 470pF; C_Disc_D3.8mm_W2.6mm_P2.50mm
C13, C14: 47uF; CP_Radial_D5.0mm_P2.50mm
C16, C17: 47pF; C_Disc_D3.8mm_W2.6mm_P2.50mm
C18, C19: 1000uF; CP_Radial_D8.0mm_P2.50mm
CX1: 0.1uF; C_Disc_D7.0mm_W2.5mm_P5.00mm
J1: AudioJack3; StereoJack_3.5mm_Switch_Ledino_KB3SPRS_Horizontal
JP1: Jumper_3_Open; PinHeader_1x03_P2.54mm_Vertical
R3, R4: 10R; R_Axial_DIN0207_L6.3mm_D2.5mm_P10.16mm_Horizontal
R5, R6: 33K; R_Axial_DIN0207_L6.3mm_D2.5mm_P10.16mm_Horizontal
RV1: 10K; Potentiometer_Alps_RK097_Dual_Horizontal
U1, U2: SN76489; DIP-16_W7.62mm
U3, U4: LM386; DIP-8_W7.62mm
X1: 3.57595Mhz; Oscillator_DIP-8

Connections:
/AMPPWR: C7.1, C8.2, C10.2, JP1.2, U3.6, U4.6
/D0: U1.10, U2.10
/D1: U1.11, U2.11
/D2: U1.12, U2.12
/D3: U1.13, U2.13
/D4: U1.15, U2.15
/D5: U1.1, U2.1
/D6: U1.2, U2.2
/D7: U1.3, U2.3
/SN_CLK: U1.14, U2.14, X1.5
/SN_L: C1.1, U2.7
/SN_R: C2.1, U1.7
/~WAIT: U1.4, U2.4
/~WR: U1.5, U2.5
GND: C3.2, C4.2, C5.2, C6.2, C7.2, C8.1, C10.1, C13.2, C14.2, C16.2, C17.2, CX1.2, RV1.3, RV1.6, U1.8, U2.8, U3.2, U3.4, U4.2, U4.4, X1.4
unnamed: C1.2, R5.1
unnamed: C2.2, R6.1
unnamed: C5.1, RV1.5, U4.3
unnamed: C6.1, RV1.2, U3.3
unnamed: C13.1, U3.7
unnamed: C14.1, U4.7
unnamed: C16.1, R3.1
unnamed: C17.1, R4.1
unnamed: C18.1, R3.2, U4.5
unnamed: C19.1, R4.2, U3.5
unnamed: R5.2, RV1.1
unnamed: R6.2, RV1.4
VCC: C3.1, C4.1, CX1.1, JP1.1, U1.16, U2.16, X1.1, X1.8

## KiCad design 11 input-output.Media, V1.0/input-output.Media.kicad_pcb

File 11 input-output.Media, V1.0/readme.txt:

This board provides video and audio capabilities using a V9938/V9958 VDP for video and PSG for multi-channel sound.  GAL information is notional and should be replaced with project specifics using Digital

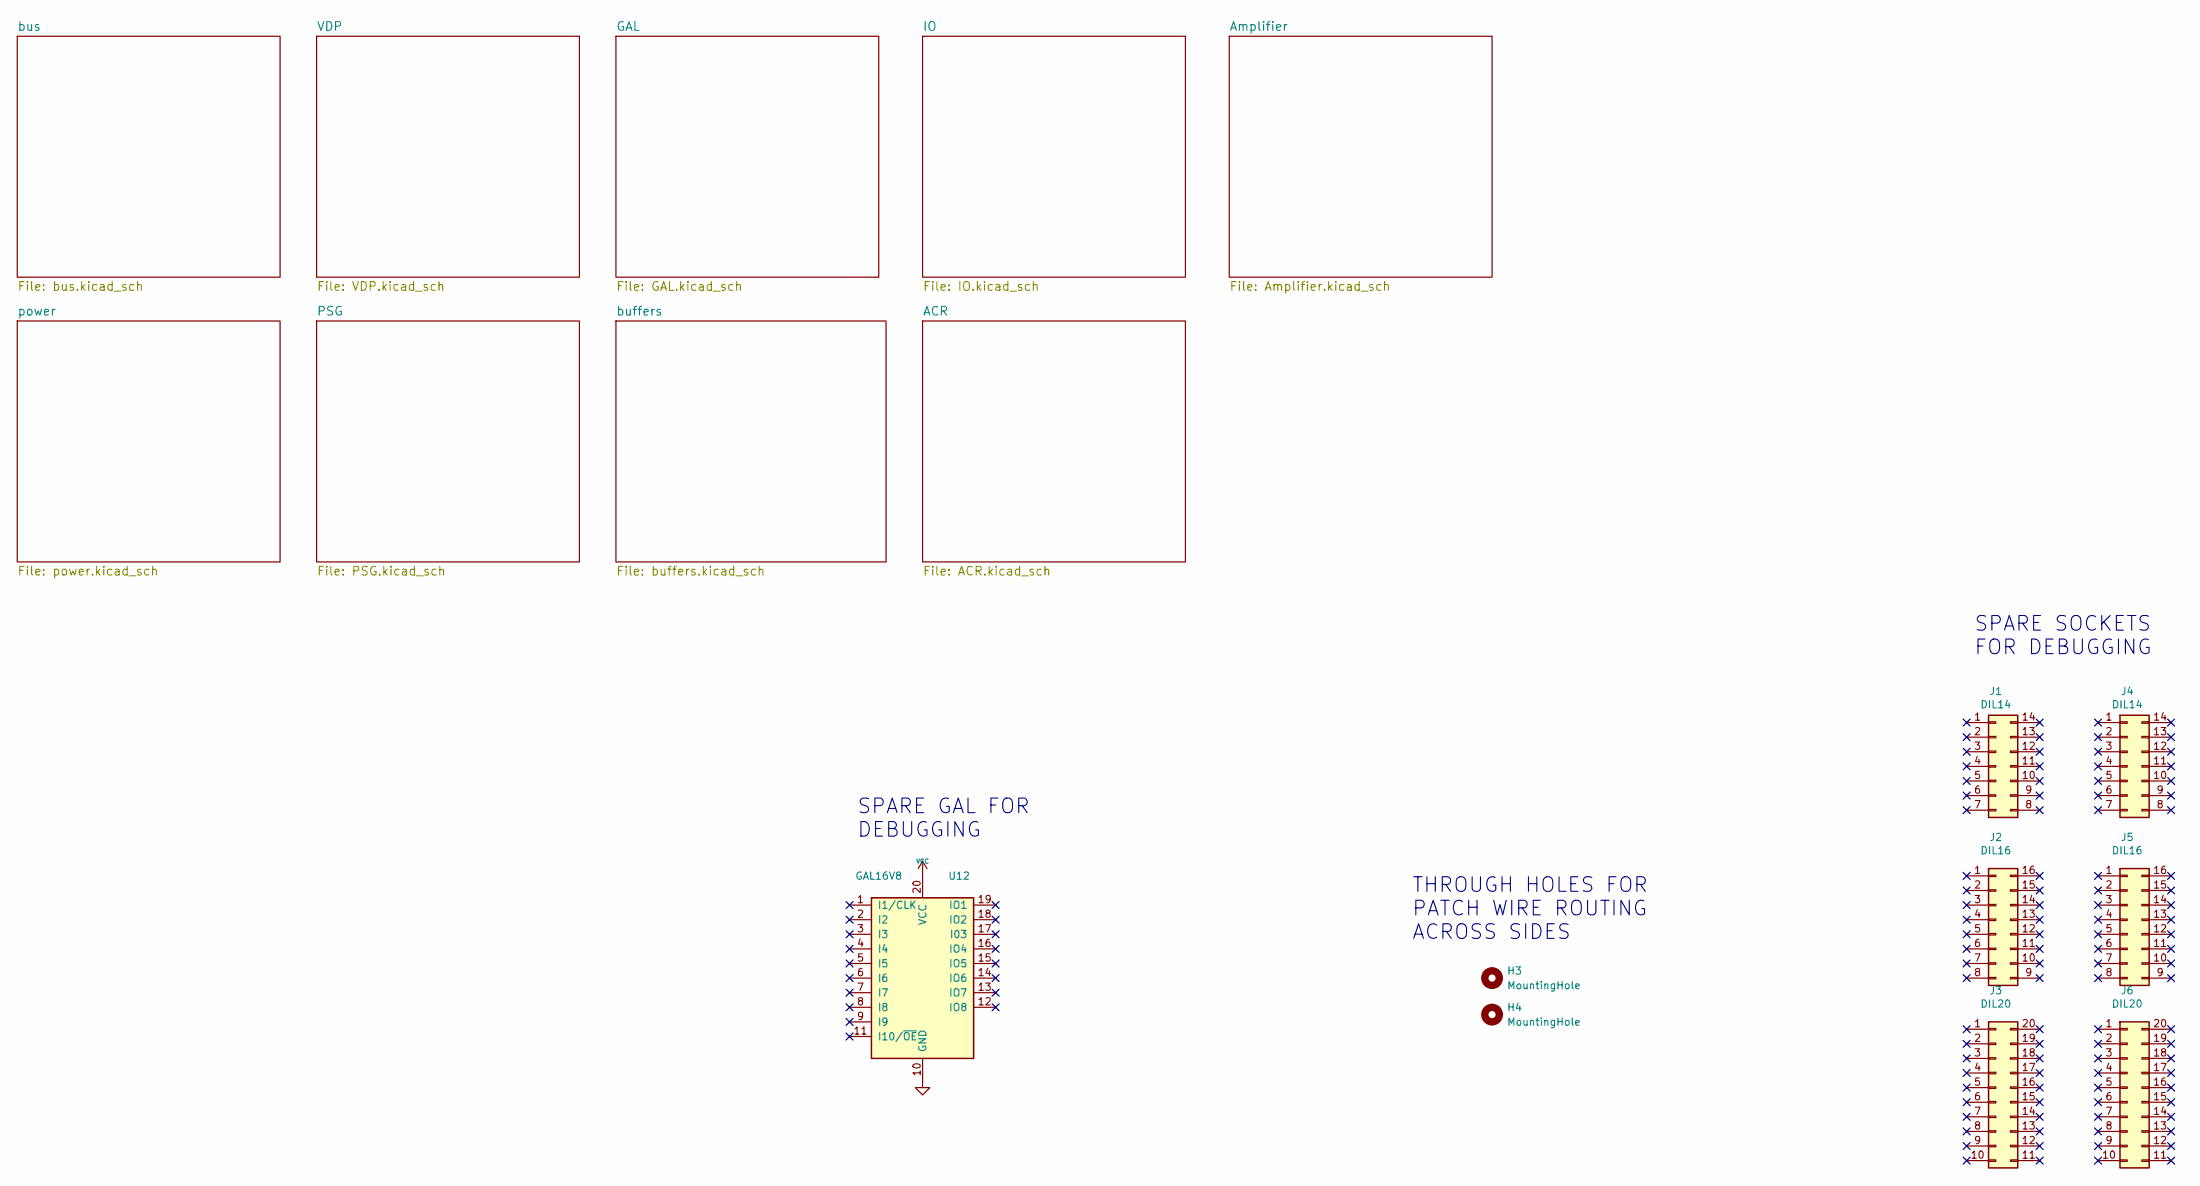
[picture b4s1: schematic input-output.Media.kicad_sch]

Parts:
H3, H4: MountingHole; MountingHole_2.2mm_M2_DIN965_Pad
J1, J4: DIL14; DIP-14_W7.62mm
J2, J5: DIL16; DIP-16_W7.62mm
J3, J6: DIL20; DIP-20_W7.62mm
U12: GAL16V8; DIP-20_W7.62mm

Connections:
GND: U12.10 (GND); also elsewhere on the board
VCC: U12.20 (VCC); also elsewhere on the board

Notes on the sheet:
THROUGH HOLES FOR PATCH WIRE ROUTING ACROSS SIDES
SPARE SOCKETS FOR DEBUGGING
SPARE GAL FOR DEBUGGING

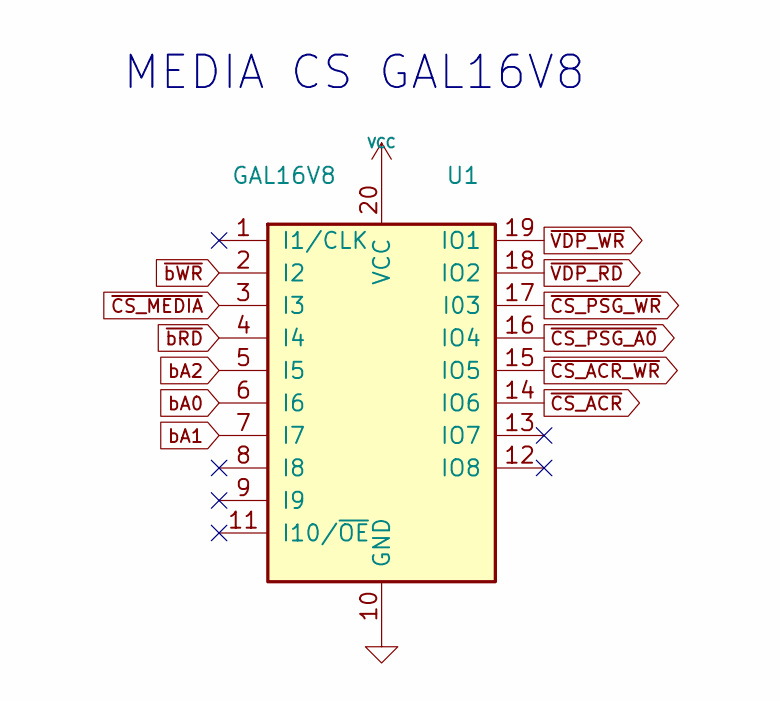
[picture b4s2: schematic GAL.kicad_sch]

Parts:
U1: GAL16V8; DIP-20_W7.62mm

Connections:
GND: U1.10 (GND); also elsewhere on the board
VCC: U1.20 (VCC); also elsewhere on the board
bA0: U1.6 (I6); also elsewhere on the board
bA1: U1.7 (I7); also elsewhere on the board
bA2: U1.5 (I5); also elsewhere on the board
~CS_ACR_WR: U1.15 (IO5); also elsewhere on the board
~CS_ACR: U1.14 (IO6); also elsewhere on the board
~CS_MEDIA: U1.3 (I3); also elsewhere on the board
~CS_PSG_A0: U1.16 (IO4); also elsewhere on the board
~CS_PSG_WR: U1.17 (I03); also elsewhere on the board
~VDP_RD: U1.18 (IO2); also elsewhere on the board
~VDP_WR: U1.19 (IO1); also elsewhere on the board
~bRD: U1.4 (I4); also elsewhere on the board
~bWR: U1.2 (I2); also elsewhere on the board

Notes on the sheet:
MEDIA CS GAL16V8
